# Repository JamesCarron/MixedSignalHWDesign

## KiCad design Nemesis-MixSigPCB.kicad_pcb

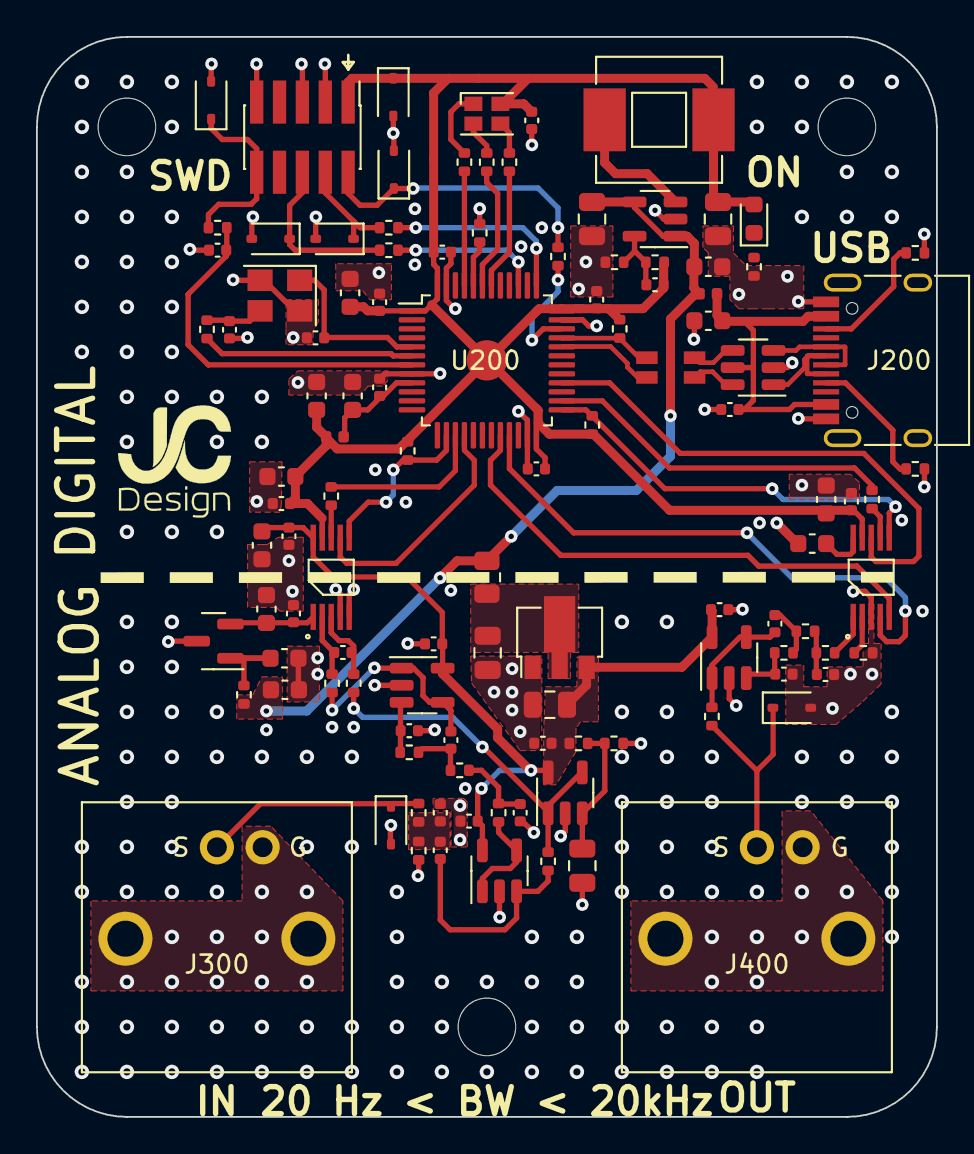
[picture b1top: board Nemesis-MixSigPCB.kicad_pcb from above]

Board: 4 copper layers, 50.0 x 60.0 mm, 113 parts (0 on the bottom side), 68 nets.

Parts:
C100, C101, C206, C207, C402: 1u; C_0603_1608Metric
C102, C103, C104, C105, C107: 22u; C_0805_2012Metric
C106: DNP; C_0402_1005Metric
C108, C201, C202, C203, C204, C210, C211, C212, C301, C302, C306, C311, C313, C314, C401, C406: 100n; C_0402_1005Metric
C200, C308, C309, C310, C312, C315, C400: 10u; C_0603_1608Metric
C205: 10n; C_0402_1005Metric
C208, C209: 10p; C_0402_1005Metric
C300, C304, C307, C404: 150p; C_0402_1005Metric
C303, C305, C403, C405: 1n; C_0402_1005Metric
D100: GREEN; LED_0603_1608Metric
D200: LED_RGB_E6C1206RGBC3UDA; LED_Cree-PLCC4_2x2mm_CW
D201, D202, D203, D204, D205, D300, D400: PESD3V3L1BA,115; D_SOD-323
H1, H2, H3: MountingHole; MountingHole_3.2mm_M3
J200: USB_C_Receptacle_USB2.0; USB_C_Receptacle_HRO_TYPE-C-31-M-12
J201: 2x5 1.27mm; PinHeader_2x05_P1.27mm_Vertical_SMD
J300, J400: 031-5640-1010; AMPHENOL-BNC-031-5640-1010
L100, L200: 10n; L_0402_1005Metric
L101: 15u; MWSA0603S
L201: CMF3216F-900-2P-T; CMC-1206
R100: 10R; R_0805_2012Metric
R101: 100k; R_0402_1005Metric
R102, R304, R403: 22k; R_0402_1005Metric
R103, R104, R105, R207, R208, R209, R300, R306, R307: 1k; R_0402_1005Metric
R200, R202, R203, R401: 10k; R_0402_1005Metric
R201, R309, R400: 0R; R_0402_1005Metric
R204: 1k5; R_0402_1005Metric
R205, R206: 5k1; R_0402_1005Metric
R210, R211, R212, R213, R308, R405: 49R9; R_0402_1005Metric
R301, R302: 2M2; R_0402_1005Metric
R303, R402: 6k8; R_0402_1005Metric
R305, R404: 12k; R_0402_1005Metric
U100: HT7533-1; SOT-89-3
U101: TLV62569DBV; SOT-23-5
U102, U300, U301, U401: MCP6001T-E/OT; SOT-23-5
U200: STM32F103CBT6; LQFP-48_7x7mm_P0.5mm
U201: USBLC6-2SC6; SOT-23-6
U302: REF3033AIDBZT; SOT-23
U303: ADC141S626CIMM_NOPB; VSSOP-10
U400: DAC7563SDGSR; VSSOP-10
Y200: 16MHz; Crystal_SMD_3225-4Pin_3.2x2.5mm

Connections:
+3.3VA: C103.1, C108.1, C302.1, C306.1, C312.1, C313.1, C406.1, R104.2, U100.3 (VOUT), U102.5 (V+), U300.5 (V+), U301.5 (V+), U303.10 (VA), U401.5 (V+)
+3V3: C105.1, C106.1, C200.1, C201.1, C202.1, C203.1, C204.1, C207.1, C211.1, C314.1, C315.1, C400.1, C401.1, D100.2 (A), D200.2, D201.1 (A1), J201.1, L101.2, L200.2, R101.2, R202.1, R203.1, R204.1, U200.1 (VBAT), U200.24 (VDD), U200.36 (VDD), U200.48 (VDD), U303.9 (VIO), U400.9 (AVDD)
+5V: C101.1, C104.1, C308.1, L100.2, R100.2, R308.2, U101.1 (EN), U101.4 (VIN)
/ADC/ADC_IN+: C307.1, R306.1, U303.2 (+IN)
/ADC/ADC_IN-: C307.2, R307.1, U303.3 (-IN)
/ADC/ADC_SCLK: R309.2, U303.8 (SCLK)
/ADC/ADC_VREF: C310.1, C311.1, U302.2 (OUT), U303.1 (VREF)
/ADC/ADC_VREF_VIN: C309.1, R308.1, U302.1 (IN)
/ADC/IN: D300.1 (A1), J300.1 (In), R300.2
/ADC/IN_AA_BUF_IN: C304.1, R305.1, U301.3 (+)
/ADC/IN_AA_BUF_OUT: C305.2, R306.2, U301.1, U301.4 (-)
/ADC/IN_BUF: C301.1, R302.1, U300.3 (+)
/ADC/IN_BUF_OUT: R303.2, U300.1, U300.4 (-)
/ADC/IN_RF: C300.1, C301.2, R300.1, R301.2
/DAC/DAC_OUT_A: R402.2, U400.1 (VOUT_A)
/DAC/DAC_OUT_B: R401.1, U400.2 (VOUT_B)
/DAC/DAC_SCLK: R400.2, U400.7 (SCLK)
/DAC/DAC_VREF: C402.1, U400.10 (VREFIN/VREFOUT)
/DAC/OUT: D400.1 (A1), J400.1 (In), R405.1
/DAC/OUT_AA_BUF_IN: C404.1, R404.1, U401.3 (+)
/DAC/OUT_AA_BUF_OUT: C405.2, R405.2, U401.1, U401.4 (-)
/MCU/BOOT0: R200.1, U200.44 (BOOT0)
/MCU/CONN_NRST: D205.1 (A1), J201.10, R213.2
/MCU/CONN_SWCLK: D203.1 (A1), J201.4, R211.2
/MCU/CONN_SWDIO: D202.1 (A1), J201.2, R210.2
/MCU/CONN_SWO: D204.1 (A1), J201.6, R212.2
/MCU/HSE_IN: C208.1, U200.5 (PD0), Y200.1
/MCU/HSE_OUT: R201.1, U200.6 (PD1)
/MCU/LED_B_K: D200.4, R209.2
/MCU/LED_G_K: D200.1, R208.2
/MCU/LED_R_K: D200.3, R207.2
/MCU/NRST: C212.1, R213.1, U200.7 (NRST)
/MCU/SWCLK: R211.1, U200.37 (PA14)
/MCU/SWDIO: R210.1, U200.34 (PA13)
/MCU/SWO: R212.1, U200.39 (PB3)
/MCU/TIM4_CH1: R207.1, U200.42 (PB6)
/MCU/TIM4_CH2: R209.1, U200.43 (PB7)
/MCU/TIM4_CH3: R208.1, U200.45 (PB8)
/MCU/USB_CMC_D+: L201.2, U201.4 (I/O2)
/MCU/USB_CMC_D-: L201.1, U201.6 (I/O1)
/MCU/USB_CONN_CC1: J200.A5 (CC1), R205.1
/MCU/USB_CONN_CC2: J200.B5 (CC2), R206.1
/MCU/USB_CONN_D+: J200.A6 (D+), J200.B6 (D+), U201.3 (I/O2)
/MCU/USB_CONN_D-: J200.A7 (D-), J200.B7 (D-), U201.1 (I/O1)
/MCU/USB_D+: L201.3, R204.2, U200.33 (PA12)
/MCU/USB_D-: L201.4, U200.32 (PA11)
/MCU/XTAL_IN: C209.1, R201.2, Y200.3
/Power/+5V_FILT: C102.1, R100.1, U100.2 (VIN)
/Power/BUCK_FB: C106.2, R101.1, R102.2, U101.5 (FB)
/Power/BUCK_SW: L101.1, U101.3 (SW)
/Power/LED_PWR_K: D100.1 (K), R103.2
/Power/VREF: C107.1, R104.1, R105.2, U102.3 (+)
DAC_NCLR: U200.20 (PB2), U400.5 (NCLR)
DAC_NLDAC: U200.21 (PB10), U400.4 (NLDAC)
GND: C100.2, C101.2, C102.2, C103.2, C104.2, C105.2, C107.2, C108.2, C200.2, C201.2, C202.2, C203.2, C204.2, C205.2, C206.2, C207.2, C208.2, C209.2, C210.2, C211.2, C212.2, C300.2, C302.2, C303.2, C304.2, C306.2, C308.2, C309.2, C310.2, C311.2, C312.2, C313.2, C314.2, C315.2, C400.2, C401.2, C402.2, C403.2, C404.2, C406.2, D201.2 (A2), D202.2 (A2), D203.2 (A2), D204.2 (A2), D205.2 (A2), D300.2 (A2), D400.2 (A2), J200.A1 (GND), J200.A12 (GND), J200.B1 (GND), J200.B12 (GND), J201.3, J201.5, J201.9, J300.2 (Ext), J400.2 (Ext), R102.1, R103.1, R105.1, R200.2, R205.2, R206.2, R301.1, R401.2, U100.1 (GND), U101.2 (GND), U102.2 (V-), U200.8 (VSSA), U200.23 (VSS), U200.35 (VSS), U200.47 (VSS), U201.2 (GND), U300.2 (V-), U301.2 (V-), U302.3 (GND), U303.4 (GND), U303.5 (GND), U400.3 (GND), U401.2 (V-), Y200.2, Y200.4
unnamed: C303.1, R303.1, R304.2
unnamed: C305.1, R304.1, R305.2
unnamed: C403.1, R402.1, R403.2
unnamed: C405.1, R403.1, R404.2
SPI1_MISO: U200.16 (PA6), U303.7 (DOUT)
SPI1_NSS: R203.2, U200.14 (PA4), U303.6 (NCS)
SPI1_SCK: R309.1, U200.15 (PA5)
SPI2_MOSI: U200.28 (PB15), U400.8 (DIN)
SPI2_NSS: R202.2, U200.25 (PB12), U400.6 (NSYNC)
SPI2_SCK: R400.1, U200.26 (PB13)
VBUS: C100.1, C210.1, J200.A4 (VBUS), J200.A9 (VBUS), J200.B4 (VBUS), J200.B9 (VBUS), L100.1, U201.5 (VBUS)
VCOM: R302.2, R307.2, U102.1, U102.4 (-)
VDDA: C205.1, C206.1, L200.1, U200.9 (VDDA)

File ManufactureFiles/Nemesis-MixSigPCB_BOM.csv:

"Id";"Designator";"Footprint";"Quantity";"Designation";"Supplier and ref";
1;"U303";"VSSOP-10";1;"ADC141S626CIMM_NOPB";;;
2;"U400";"VSSOP-10";1;"DAC7563SDGSR";;;
3;"C303,C305,C403,C405";"C_0402_1005Metric";4;"1n";;;
4;"C105,C104,C103,C102,C107";"C_0805_2012Metric";5;"22u";;;
5;"R304,R403,R102";"R_0402_1005Metric";3;"22k";;;
6;"C306,C202,C302,C212,C201,C203,C210,C313,C314,C108,C211,C406,C401,C301,C204,C311";"C_0402_1005Metric";16;"100n";;;
7;"R301,R302";"R_0402_1005Metric";2;"2M2";;;
8;"D202,D201,D300,D204,D400,D205,D203";"D_SOD-323";7;"PESD3V3L1BA,115";;;
9;"R103,R207,R306,R300,R105,R209,R104,R208,R307";"R_0402_1005Metric";9;"1k";;;
10;"U200";"LQFP-48_7x7mm_P0.5mm";1;"STM32F103CBT6";;;
11;"R305,R404";"R_0402_1005Metric";2;"12k";;;
12;"R303,R402";"R_0402_1005Metric";2;"6k8";;;
13;"U102,U401,U301,U300";"SOT-23-5";4;"MCP6001T-E/OT";;;
14;"R213,R211,R308,R212,R405,R210";"R_0402_1005Metric";6;"49R9";;;
15;"C200,C400,C312,C310,C308,C315,C309";"C_0603_1608Metric";7;"10u";;;
16;"R201,R309,R400";"R_0402_1005Metric";3;"0R";;;
17;"R205,R206";"R_0402_1005Metric";2;"5k1";;;
18;"C206,C100,C101,C207,C402";"C_0603_1608Metric";5;"1u";;;
19;"R100";"R_0805_2012Metric";1;"10R";;;
20;"J201";"PinHeader_2x05_P1.27mm_Vertical_SMD";1;"2x5 1.27mm";;;
21;"D100";"LED_0603_1608Metric";1;"GREEN";;;
22;"C209,C208";"C_0402_1005Metric";2;"10p";;;
23;"J200";"USB_C_Receptacle_HRO_TYPE-C-31-M-12";1;"USB_C_Receptacle_USB2.0";;;
24;"J400,J300";"AMPHENOL-BNC-031-5640-1010";2;"031-5640-1010";;;
25;"U101";"SOT-23-5";1;"TLV62569DBV";;;
26;"L101";"MWSA0603S";1;"15u";;;
27;"Y200";"Crystal_SMD_3225-4Pin_3.2x2.5mm";1;"16MHz";;;
28;"C307,C404,C300,C304";"C_0402_1005Metric";4;"150p";;;
29;"U302";"SOT-23";1;"REF3033AIDBZT";;;
30;"R202,R203,R200,R401";"R_0402_1005Metric";4;"10k";;;
31;"H2,H1,H3";"MountingHole_3.2mm_M3";3;"MountingHole";;;
32;"L200,L100";"L_0402_1005Metric";2;"10n";;;
33;"R204";"R_0402_1005Metric";1;"1k5";;;
34;"C106";"C_0402_1005Metric";1;"DNP";;;
35;"L201";"CMC-1206";1;"CMF3216F-900-2P-T";;;
36;"C205";"C_0402_1005Metric";1;"10n";;;
37;"U100";"SOT-89-3";1;"HT7533-1";;;
38;"R101";"R_0402_1005Metric";1;"100k";;;
39;"U201";"SOT-23-6";1;"USBLC6-2SC6";;;
40;"D200";"LED_Cree-PLCC4_2x2mm_CW";1;"LED_RGB_E6C1206RGBC3UDA";;;

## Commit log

2023-03-23 Revert "Initial commit"
    This reverts commit 2847ec419cc848ff79c3945161a6fec249cbedf5.
2023-03-23 Initial Component Layout
    Initial Component Layout
2023-03-23 Routed uController Basic Tracks
2023-03-23 Initial Ground Pours done
2023-05-23 Ignored KiCAD Backups Folder
2023-05-23 Routed Digital Side of Board
2023-05-23 Minor tweaks to digital side PCB routing
2023-08-19 Completed Analog Routing
2023-08-19 Remedied DRC issues
    Missing footprints and the following issue
    https://forum.kicad.info/t/drc-footprint-component-type-doesnt-match-footprint-pad/40404
2023-08-19 AddedManufactureFiles
